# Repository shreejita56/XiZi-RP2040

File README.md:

# XiZi Rp2040

So I made on a Dev-board based on Rp-2040 with similar size constrain like Xiao-Rp2040. So I used the smallest size of resistors and capacitors . It has access to a total of 14 GPI0 and 4 Analog . 4 Pins act as dual purpose. It holds an USB-C Type interference for communication and 3.3V Voltage regulator and Crystal oscillator , Flash Memory , boot Switch  and more . 

## Why This

I made this as an alternative for  Xiao-Rp2040. Every time we need a small rp2040 microcontroller we surely need to go with Xiao boards . I made this so that I could use it for my upcoming projects related to Micro pad  and other IOT related things.

## Features

- Based on RP-2040 Chip
- Has MCP1700x-330xxTT as Voltage Regulator 
- Has W25Q16JVUXIQTR as Flash Memory
- Has 2 set of 8 connector pins  
- Has pin connector has access for GND and 3.3V
- It is compatible to a breadboard 

## Cost Summary (BOM)

### Components

| Designation | Comment | Quantity | Price (USD) | Link |
|---|---|---:|---:|---|
| C1 | 1uF | 20 | $0.17 | [JLCPCB](https://jlcpcb.com/partdetail/TaiyoYuden-JMK063ABJ105MPF/C87143) |
| C13, C14 | 10uF | 6 | $1.1376 | [JLCPCB](https://jlcpcb.com/partdetail/KyoceraAVX-TAJA106K016RNJ/C7171) |
| C15, C16 | 33pF | 20 | $0.0720 | [JLCPCB](https://jlcpcb.com/partdetail/MurataElectronics-GRM0335C1H330JA01D/C76925) |
| C17, C2, C3, C4 | 0.1uF | 28 | $0.1372 | [JLCPCB](https://jlcpcb.com/partdetail/68025-0201X104K6R3NT/C66938) |
| D1 | LED | 10 | $0.69 | [JLCPCB](https://jlcpcb.com/partdetail/XINGLIGHT-XL0201SURC/C3646923) |
| J1 | USB_C_Receptacle_USB2.0_16P | 2 | $0.8590 | [JLCPCB](https://jlcpcb.com/partdetail/HOOYA-USB_306_BSU/C309338) |
| R1, R2 | 33R | 20 | $0.0280 | [JLCPCB](https://jlcpcb.com/partdetail/301748-RC01W33R0FT/C320843) |
| R3, R8 | 5.1K | 20 | $0.0240 | [JLCPCB](https://jlcpcb.com/partdetail/479853-0201WMJ0512TEE/C473460) |
| R4 | 5.1K | 20 | $0.0240 | [JLCPCB](https://jlcpcb.com/partdetail/479853-0201WMJ0512TEE/C473460) |
| R5, R6 | 1K | 20 | $0.0240 | [JLCPCB](https://jlcpcb.com/partdetail/SAE-1RC0201J0102/C54530604) |
| R7 | 10K | 20 | $0.0260 | [JLCPCB](https://jlcpcb.com/partdetail/SAE-1RC0201F1002/C54530535) |
| U1 | RP2040 | 2 | $2.1488 | [JLCPCB](https://jlcpcb.com/partdetail/RaspberryPi-RP2040/C2040) |
| U2 | MCP1700x-330xxTT | 5 | $2.3595 | [JLCPCB](https://jlcpcb.com/partdetail/MicrochipTech-MCP1700T_3302ETT/C39051) |
| U4 | W25Q16JVUXIQTR | 2 | $2.3546 | [JLCPCB](https://jlcpcb.com/partdetail/WinbondElec-W25Q16JVSSIQ/C82317) |
| Y1 | 12MHz | 6 | $0.3756 | [JLCPCB](https://jlcpcb.com/partdetail/C55155400) |

### PCB Charges 

| Charge | Quantity | Price (USD) |
|---|---:|---:|
| PCB Price | 1 | $4.00 |
| Standard PCBA Price | 1 | $67.63 |
| Setup Fee | 1 | $25.75 |
| Stencil | 1 | $8.27 |
| Panel | 1 | $0.00 |
| Large Size | 1 | $0.00 |
| Components (14 items) | 1 | $10.41 |
| Feeders Loading Fee | 1 | $21.70 |
| SMT Assembly | 1 | $0.94 |
| Packaging Fee | 1 | $0.50 |
| Special Components Fee | 1 | $0.06 |
| Shipping | 1 | $11.47 |

###   Total
| Description | Price (USD) |
|---|---:|
| PCB Price | $4.00 |
| Standard PCBA Price | $67.63 |
| Shipping | $11.47 |
| **Total Estimated Cost** | **$83.10** |

### Schematic

### PCB Design

### 3D Design

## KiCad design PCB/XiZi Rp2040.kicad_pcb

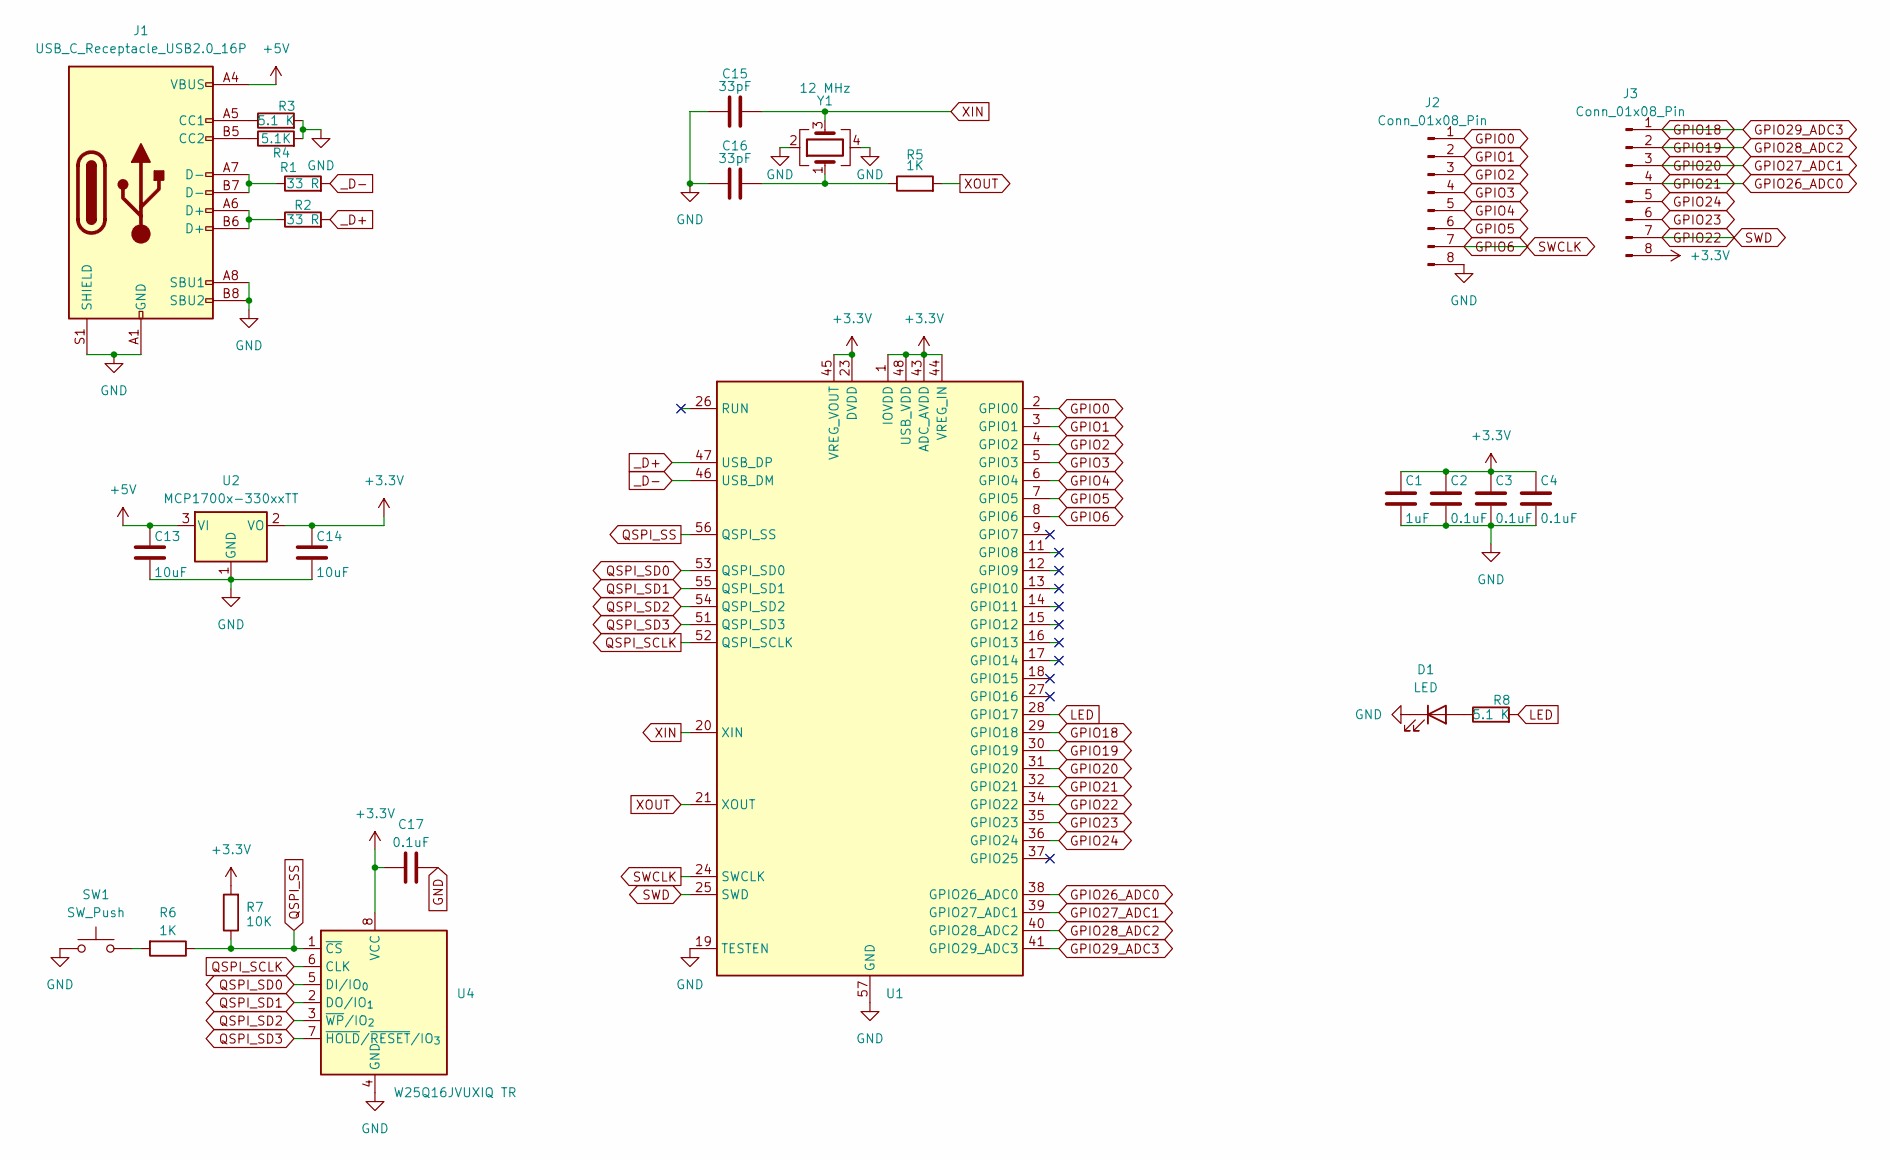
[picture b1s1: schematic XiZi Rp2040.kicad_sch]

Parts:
C1: 1uF; C_0201_0603Metric
C2, C3, C4, C17: 0.1uF; C_0201_0603Metric
C13, C14: 10uF; C_0201_0603Metric
C15, C16: 33pF; C_0201_0603Metric
D1: LED; LED_0201_0603Metric
J1: USB_C_Receptacle_USB2.0_16P; USB_C_Receptacle_G-Switch_GT-USB-7010ASV
J2, J3: Conn_01x08_Pin; Molex_SL_171971-0008_1x08_P2.54mm_Vertical
R1, R2: 33 R; R_0201_0603Metric
R3, R8: 5.1 K; R_0201_0603Metric
R4: 5.1K; R_0201_0603Metric
R5, R6: 1K; R_0201_0603Metric
R7: 10K; R_0201_0603Metric
SW1: SW_Push; SW_Push_SPST_NO_Alps_SKRK
U1: RP2040; QFN-56-1EP_7x7mm_P0.4mm_EP3.2x3.2mm
U2: MCP1700x-330xxTT; SOT-23
U4: W25Q16JVUXIQ TR; Winbond_USON-8-1EP_3x2mm_P0.5mm_EP0.2x1.6mm
Y1: 12 MHz; Crystal_SMD_1210-4Pin_1.2x1.0mm

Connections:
+3.3V: C1.1, C2.1, C3.1, C4.1, C14.1, C17.1, J3.8, R7.2, U1.1 (IOVDD), U1.10 (IOVDD), U1.22 (IOVDD), U1.23 (DVDD), U1.33 (IOVDD), U1.42 (IOVDD), U1.43 (ADC_AVDD), U1.44 (VREG_IN), U1.45 (VREG_VOUT), U1.48 (USB_VDD), U1.49 (IOVDD), U1.50 (DVDD), U2.2 (VO), U4.8 (VCC)
+5V: C13.1, J1.A4 (VBUS), J1.A9 (VBUS), J1.B4 (VBUS), J1.B9 (VBUS), U2.3 (VI)
GND: C1.2, C2.2, C3.2, C4.2, C13.2, C14.2, C15.1, C16.1, C17.2, D1.1 (K), J1.A1 (GND), J1.A8 (SBU1), J1.A12 (GND), J1.B1 (GND), J1.B8 (SBU2), J1.B12 (GND), J1.S1 (SHIELD), J2.8, R3.2, R4.2, SW1.1, U1.19 (TESTEN), U1.57 (GND), U2.1 (GND), U4.4 (GND), Y1.2, Y1.4
GPIO0: J2.1, U1.2 (GPIO0)
GPIO1: J2.2, U1.3 (GPIO1)
GPIO2: J2.3, U1.4 (GPIO2)
GPIO3: J2.4, U1.5 (GPIO3)
GPIO4: J2.5, U1.6 (GPIO4)
GPIO5: J2.6, U1.7 (GPIO5)
GPIO6: J2.7, U1.8 (GPIO6), U1.24 (SWCLK)
GPIO18: J3.1, U1.29 (GPIO18), U1.41 (GPIO29_ADC3)
GPIO19: J3.2, U1.30 (GPIO19), U1.40 (GPIO28_ADC2)
GPIO20: J3.3, U1.31 (GPIO20), U1.39 (GPIO27_ADC1)
GPIO21: J3.4, U1.32 (GPIO21), U1.38 (GPIO26_ADC0)
GPIO22: J3.7, U1.25 (SWD), U1.34 (GPIO22)
GPIO23: J3.6, U1.35 (GPIO23)
GPIO24: J3.5, U1.36 (GPIO24)
LED: R8.2, U1.28 (GPIO17)
unnamed: C16.2, R5.1, Y1.1
unnamed: D1.2 (A), R8.1
unnamed: J1.A5 (CC1), R3.1
unnamed: J1.B5 (CC2), R4.1
unnamed: J1.A6 (D+), J1.B6 (D+), R2.1
unnamed: J1.A7 (D-), J1.B7 (D-), R1.1
unnamed: R6.2, SW1.2
QSPI_SCLK: U1.52 (QSPI_SCLK), U4.6 (CLK)
QSPI_SD0: U1.53 (QSPI_SD0), U4.5 (DI/IO_{0})
QSPI_SD1: U1.55 (QSPI_SD1), U4.2 (DO/IO_{1})
QSPI_SD2: U1.54 (QSPI_SD2), U4.3 (~WP/IO_{2})
QSPI_SD3: U1.51 (QSPI_SD3), U4.7 (~HOLD/~RESET/IO_{3})
QSPI_SS: R6.1, R7.1, U1.56 (QSPI_SS), U4.1 (~CS)
XIN: C15.2, U1.20 (XIN), Y1.3
XOUT: R5.2, U1.21 (XOUT)
_D+: R2.2, U1.47 (USB_DP)
_D-: R1.2, U1.46 (USB_DM)

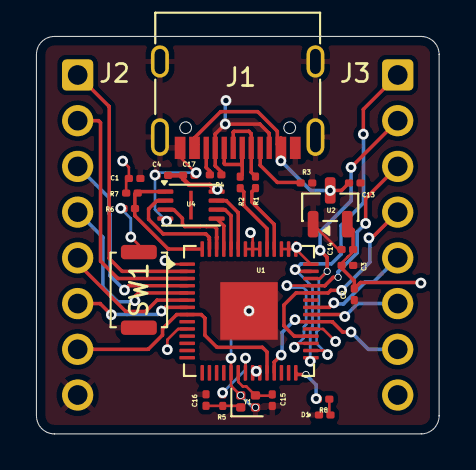
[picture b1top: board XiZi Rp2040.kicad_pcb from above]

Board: 2 copper layers, 22.4 x 22.1 mm, 26 parts (0 on the bottom side), 35 nets.

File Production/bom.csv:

Designator,Footprint,Quantity,Value,LCSC Part #
C1,0201,1,1uF,
"C13, C14",0201,2,10uF,
"C15, C16",0201,2,33pF,
"C17, C2, C3, C4",0201,4,0.1uF,
D1,0201,1,LED,
J1,USB_C_Receptacle_G-Switch_GT-USB-7010ASV,1,USB_C_Receptacle_USB2.0_16P,
"J2, J3",Molex_SL_171971-0008_1x08_P2.54mm_Vertical,2,Conn_01x08_Pin,
"R1, R2",0201,2,33 R,
"R3, R8",0201,2,5.1 K,
R4,0201,1,5.1K,
"R5, R6",0201,2,1K,
R7,0201,1,10K,
SW1,SW_Push_SPST_NO_Alps_SKRK,1,SW_Push,
U1,QFN-56-1EP_7x7mm_P0.4mm_EP3.2x3.2mm,1,RP2040,
U2,SOT-23,1,MCP1700x-330xxTT,
U4,Winbond_USON-8-1EP_3x2mm_P0.5mm_EP0.2x1.6mm,1,W25Q16JVUXIQ TR,
Y1,Crystal_SMD_1210-4Pin_1.2x1.0mm,1,12 MHz,
